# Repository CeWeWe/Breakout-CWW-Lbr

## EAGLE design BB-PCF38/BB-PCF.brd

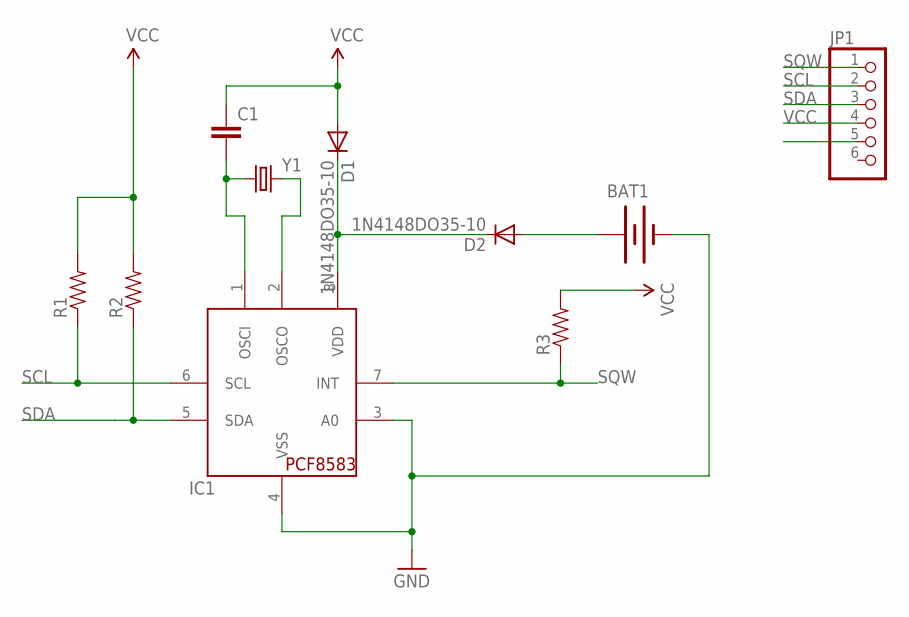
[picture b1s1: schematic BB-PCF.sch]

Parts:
BAT1: BATTERY20PTH; BATTCOM_20MM_PTH
C1: CAPPTH; CAP-PTH-SMALL
D1, D2: 1N4148DO35-10; DO35-10
IC1: PCF8583; DIL08
JP1: PINHD-1X6; 1X06
R1, R2, R3: RESISTORPTH-1/4W; AXIAL-0.4
Y1: CRYSTALTC26H_EZ; TC26HEZ

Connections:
GND: BAT1.2 (-), IC1.3 (A0), IC1.4 (VSS), JP1.5
unnamed: D1.C, D2.C, IC1.8 (VDD)
unnamed: BAT1.1 (+), D2.A
unnamed: C1.2, IC1.1 (OSCI), Y1.1
unnamed: IC1.2 (OSCO), Y1.2
SCL: IC1.6 (SCL), JP1.2, R1.P$1 (1)
SDA: IC1.5 (SDA), JP1.3, R2.P$1 (1)
SQW: IC1.7 (INT), JP1.1, R3.P$1 (1)
VCC: C1.1, D1.A, JP1.4, R1.P$2 (2), R2.P$2 (2), R3.P$2 (2)

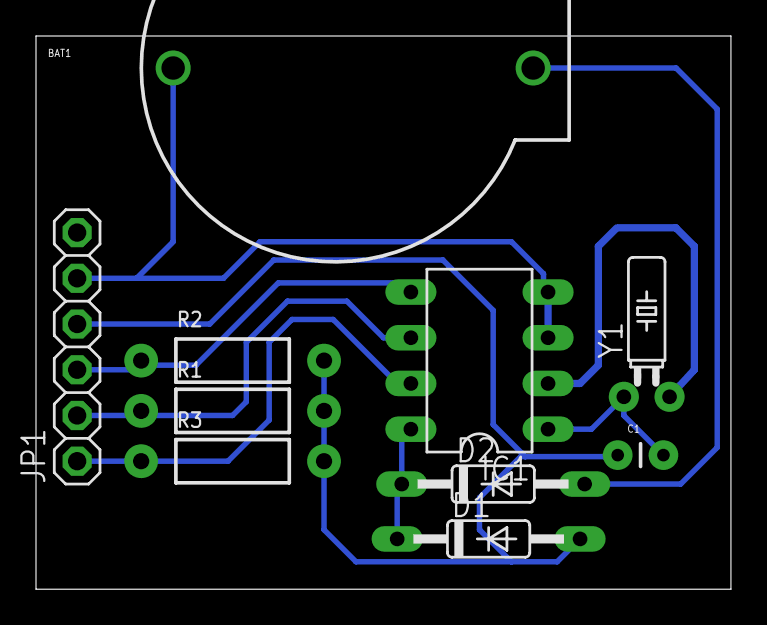
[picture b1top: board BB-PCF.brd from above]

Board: 2 copper layers, 38.6 x 30.7 mm, 10 parts (0 on the bottom side), 9 nets.

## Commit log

2015-04-30 Version 0.1

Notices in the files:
parts and their libraries:
SparkFun-Resistors: Licensing: CC v3.0 Share-Alike You are welcome to use this library for commercial purposes.
